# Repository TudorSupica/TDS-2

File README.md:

# The [TDS-2](https://github.com/TudorSupica/TDS-2/)

The TDS-2 is the next guitar pedal in the TDS series, with an improved design and use of a standard enclosure.

The main features of the TDS-2 are the use of clipping diodes and a buffering stage, before the op-amp that amplifies the base signal. I've also used a 3PDT footswitch and some audio jacks that hold the line low when no jack is inserted, just to make sure i don't get any unecessary noise.

# Summary

The main features of the circuit are: 

- Buffer stage
- High amplification factor
- Clipping diodes
- Decoupling and bypass capacitors
- Standardised jack sockets, they pull the line low when not in use
- Barrel jack for power 
- 3PDT footswitch 
- Hammond 1590B Al enclosure

# [The Schematic](https://github.com/TudorSupica/TDS-2/blob/main/schematic/)

The principle behind the TDS-2 distortion pedal is a high amplification factor. The TL072 IC has two op-amps. The first one is used as a buffer so that the imput signal is high enough. The second op-amp actually amplifies the signal, since it's in a inverting configuration to counter the phase shift of the buffer stage. 
The amplification factor is given by the potentiometer that connects the oputput back to the inverting input. The capacitors are used to decouple and "delete" any DC voltage that might be present. I used two fast switching diodes to make a clipping stage, to ensure that the signal never goes above and below the +4,5v and -4,5v headroom.

# [The PCB](https://github.com/TudorSupica/TDS-2/blob/main/PCB/)

The PCB also has four M3 mounting holes that are connected directly to 0v, so that when I mount it in the enclosure, the aluminium enclosure gets grounded and acts like an EMF shield.
One thing I'd improve upon are the traces since they're quite narrow and may be prone to high levels of noise.

# The Hammond 1590B enclosure

The enclosure I picked for this pedal and subsequent versions of it is the Hammond 1590B, since it's made out of aluminium it's relatively cheap and effective. The enclosure offers more of a professional look to the pedal whilst also doubling as protection against EMF and other elements.

I used this datasheet to get the dimensions needed for the PCB, and i found that 10cm x 5cm is more than enough. 

This project is not intended for beginners, but with a little guidance it can be a successful starting project.

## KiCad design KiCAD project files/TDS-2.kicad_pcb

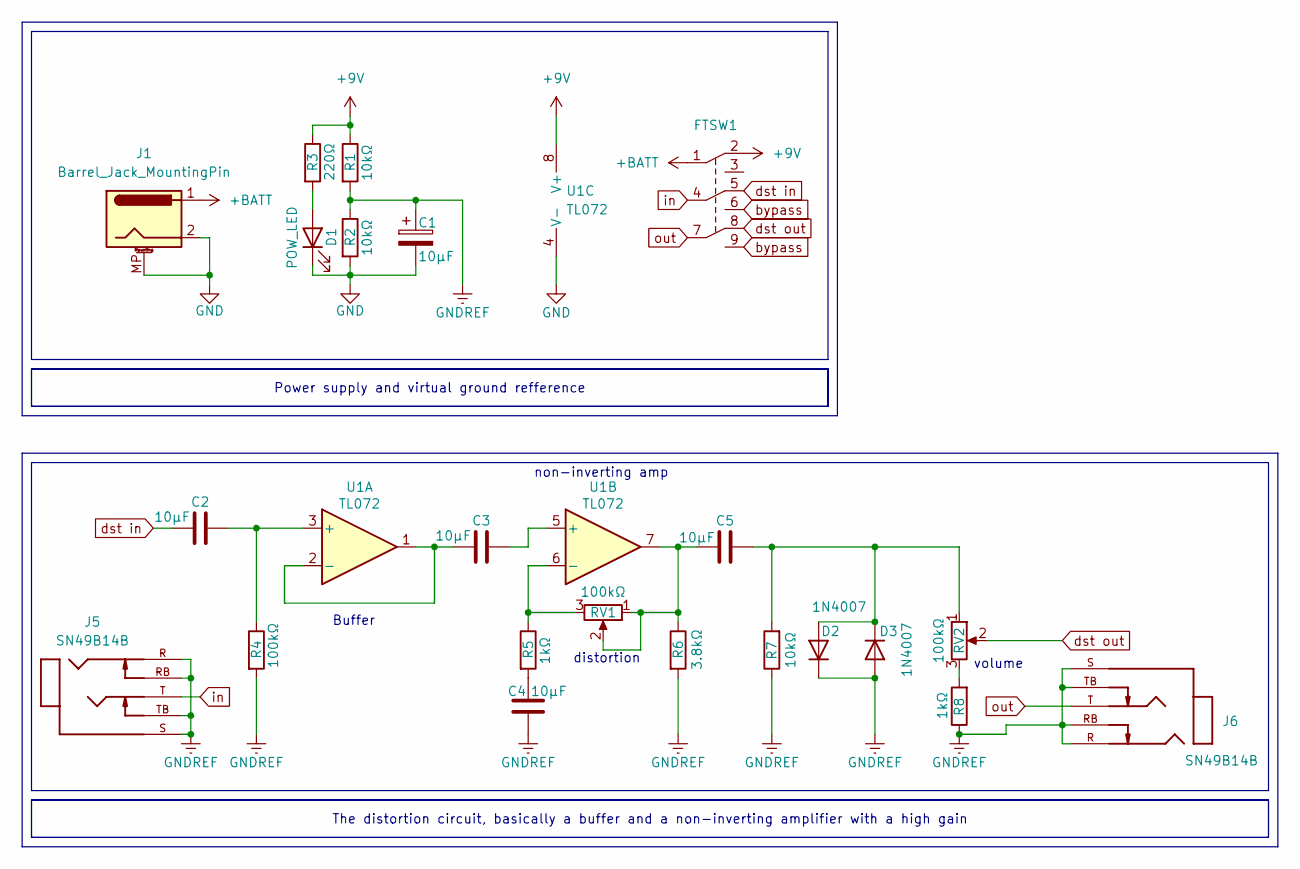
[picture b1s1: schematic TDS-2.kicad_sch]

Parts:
C1: 10µF; CP_Radial_D5.0mm_P2.50mm
C2, C3, C4, C5: 10µF; C_Disc_D4.3mm_W1.9mm_P5.00mm
D1: POW_LED; LED_D5.0mm
D2, D3: 1N4007; D_DO-41_SOD81_P10.16mm_Horizontal
FTSW1: 3PDT Footswitch
J1: Barrel_Jack_MountingPin; BarrelJack_Kycon_KLDX-0202-xC_Horizontal
J5, J6: SN49B14B; PJ-644C; PARTREV F
R1, R2, R7: 10kΩ; R_Axial_DIN0207_L6.3mm_D2.5mm_P10.16mm_Horizontal
R3: 220Ω; R_Axial_DIN0207_L6.3mm_D2.5mm_P10.16mm_Horizontal
R4: 100kΩ; R_Axial_DIN0207_L6.3mm_D2.5mm_P10.16mm_Horizontal
R5, R8: 1kΩ; R_Axial_DIN0207_L6.3mm_D2.5mm_P10.16mm_Horizontal
R6: 3.8kΩ; R_Axial_DIN0207_L6.3mm_D2.5mm_P10.16mm_Horizontal
RV1, RV2: 100kΩ; Potentiometer_Alpha_RD901F-40-00D_Single_Vertical
U1: TL072; DIP-8_W7.62mm

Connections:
+9V: FTSW1.2, R1.1, R3.1, U1.8 (V+)
+BATT: FTSW1.1, J1.1
GND: C1.2, D1.1 (K), J1.2, J1.MP (MountPin), R2.2, U1.4 (V-)
GNDREF: C1.1, C4.1, D2.1 (K), D3.2 (A), J5.R, J5.RB, J5.S, J5.TB, J6.R, J6.RB, J6.S, J6.TB, R1.2, R2.1, R4.2, R6.2, R7.1, R8.1
unnamed: C4.2, R5.2
unnamed: C5.1, R6.1, RV1.1, RV1.2, U1.7
unnamed: D1.2 (A), R3.2
unnamed: C5.2, D2.2 (A), D3.1 (K), R7.2, RV2.1
unnamed: R8.2, RV2.3
unnamed: C2.2, R4.1, U1.3 (+)
unnamed: C3.1, U1.1, U1.2 (-)
unnamed: C3.2, U1.5 (+)
unnamed: R5.1, RV1.3, U1.6 (-)
bypass: FTSW1.6, FTSW1.9
dst in: C2.1, FTSW1.5
dst out: FTSW1.8, RV2.2
in: FTSW1.4, J5.T
out: FTSW1.7, J6.T

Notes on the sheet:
The distortion circuit, basically a buffer and a non-inverting amplifier with a high gain
Power supply and virtual ground refference
volume
non-inverting amp
distortion
Buffer

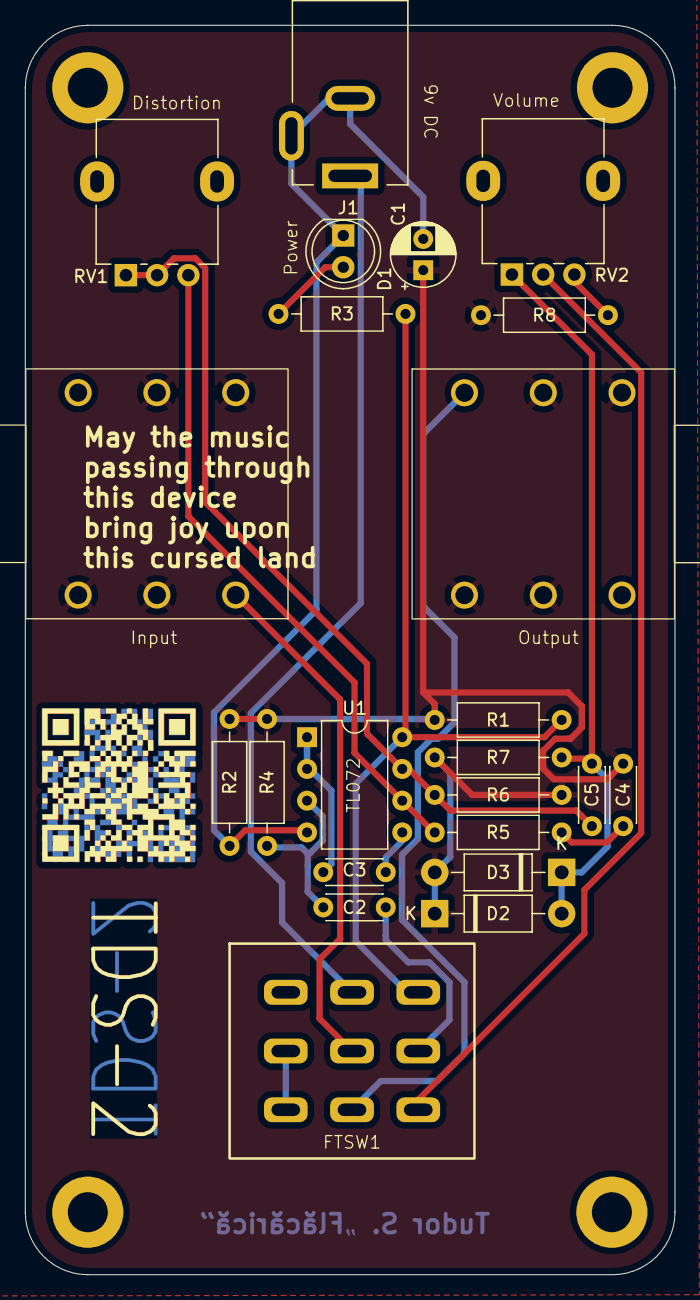
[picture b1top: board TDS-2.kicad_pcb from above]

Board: 2 copper layers, 52.0 x 100.0 mm, 23 parts (0 on the bottom side), 18 nets.

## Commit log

2024-07-09 Added schematic and made the layout for the PCB
2024-07-10 Added schematic and PCB design
2024-07-24 Moved the template file
2024-08-24 Changed the ground values
2024-08-24 Updated PDF schematic
2024-08-24 schematic
2024-11-19 Update
    Updated the schematic, idk about the photos tho
2024-12-01 Update
    I updated the schematic PDF and the photo renders of the board
